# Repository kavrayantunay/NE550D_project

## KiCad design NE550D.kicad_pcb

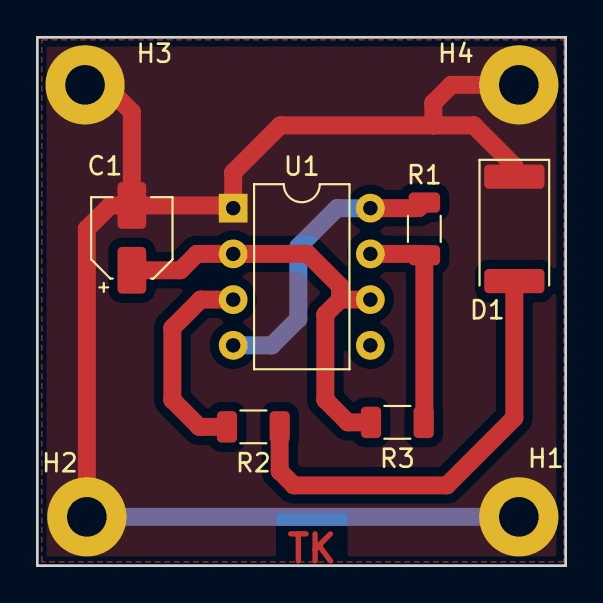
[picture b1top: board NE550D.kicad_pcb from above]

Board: 2 copper layers, 29.3 x 29.3 mm, 10 parts (0 on the bottom side), 6 nets.

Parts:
C1: 1uF; CP_Elec_4x3
D1: LED; LED_2512_6332Metric
H1, H2, H3, H4: MountingHole_Pad; MountingHole_2.2mm_M2_Pad
R1, R2: 1K; R_1206_3216Metric
R3: 470K; R_1206_3216Metric
U1: NE555P; DIP-8_W7.62mm

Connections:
+9V: R1.1, U1.4 (R), U1.8 (VCC)
GND: C1.2, D1.1 (K), H1.1, H2.1, H3.1, H4.1, U1.1 (GND)
unnamed: C1.1, R3.2, U1.2 (TR), U1.6 (THR)
unnamed: D1.2 (A), R2.2
unnamed: R1.2, R3.1, U1.7 (DIS)
unnamed: R2.1, U1.3 (Q)
